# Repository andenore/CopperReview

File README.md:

# CopperReview

[Open CopperReview on GitHub Pages](https://andenore.github.io/CopperReview/).

A review tool for CopperScript designs with two halves that can be open at once:

- **Electrical review** — generated **Schematic** sheets, the **Power** hierarchy and
  **Buses**, from the compiled electrical IR (no layout needed). Double-click or press
  N to note the selection; notes show as numbered markers. See the
  [electrical workflow and contracts](docs/electrical-review.md).
- **Layout review** — the board's placement and routing from a CopperScript board
  export: select components, nets and regions, annotate them, and export a review for
  the next LLM-assisted solver iteration.

**Assembly** (A) uses the same board to track a manual build part by part; see
[Assembly tracking](#assembly-tracking). A CopperScript run's `route-report.json` adds an
**EMI screening** layer to the board: hot loop, switch-node copper and victim pads with the
findings' numbers and conducted spectrum, all screening estimates; see
[EMI screening](#emi-screening). **Simulation** (M) reads a `copper sim` run's
`sim-results.json` on its own, no board needed: benches with their verdicts, failing limits first,
and each bench's plots drawn interactively; see [Simulation results](#simulation-results).

The **Electrical · Layout · Both** switch in the top bar picks what is shown (E, L, B).
**Both** puts the schematic and the board side by side with a draggable divider;
selecting a part or net on either side selects and centres it on the other. Parts
match by CopperScript path (or reference) and nets by name; the top bar counts parts
found on only one side (Both stays off when they share no part), and nothing proves the board was built from that exact source.
Outside **Both**, **Show on board** and **Show in schematic** (S) jump across, and
**Source** opens the declaration in the CopperScript project (found by searching the
compiled sources, since the IR does not record source lines yet), with **Open on
GitHub** at the pinned commit or **Open in VS Code** for a project served locally.

Everything opens from one **Open** menu, or by dropping files on the page:
**File…** (Ctrl+O) recognizes a board export, compiled IR, `.copper` source, saved
scene, layout review, electrical review, CopperScript issue list, run report
(`route-report.json`) or simulation results (`sim-results.json` and its CSVs) by its contents,
and accepts several at once. Opening a board keeps the open schematic, and the other
way round. **Project folder…** compiles a local project (the folder holding
`board.copper` and `copper.mod`) in the browser: sources never leave the computer,
and only dependencies pinned in `copper.lock` are downloaded from GitHub and checked
against the lock; re-pick the folder after editing. **From URL or GitHub…** compiles
GitHub source projects with local imports and pinned dependencies, or opens direct
HTTPS design files; private repositories need a fine-grained token with Contents:
Read-only (⋯ → **Private GitHub access**), kept in the tab and sent only to
`api.github.com`. See [URL loading and provenance](docs/wasm-hosting.md#open-from-url).
**Export** writes the layout review, the electrical review or the board scene; ⋯
holds the compiler check, the review limits and **Dark mode** (the page is light by
default; the choice is remembered in this browser).

This is a **separate Git project**. Its static browser build reuses CopperScript's
Rust compiler, ERC and queries through a bundled WebAssembly worker. No native
CopperScript installation or hosted backend is required by that build. The local
Python 3.11+ server additionally reads raw `.kicad_pcb` files without KiCad.
See [WASM build, static hosting and current boundaries](docs/wasm-hosting.md).
The board is read-only. Feedback never edits the PCB or solver constraints.

## Run

On Ubuntu (or anywhere with `make`, [uv](https://docs.astral.sh/uv/) and Node.js 20+):

```bash
make setup                                   # check tools, install, fetch the browser compiler
make serve PROJECT=../BysseControl-32        # compile a project folder; reload to recompile
make serve PROJECT=../BysseControl-32 HOST=0.0.0.0 OPEN=no   # reachable from other machines
make serve PROJECT=../BysseControl-32 BOARD=../BysseControl-32/build/board.kicad_pcb   # schematic and board, linked
make serve IR=build/electrical.ir.json       # or a compiled IR; BOARD=… alone for a PCB
make serve BOARD=run/board.kicad_pcb REPORT=run/route-report.json   # board with its EMI screening
make serve SIM=build/sim/sim-results.json    # a copper sim run in the Simulation view
make test
```

`PORT` (default 8769), `ENTRY` (board file in a multi-board project) and `STAGE`
(for `BOARD`) are also accepted; `make help` lists the targets. The compiler is
fetched on first use and again whenever `.copperscript-version` changes.

Or run the commands directly. From this repository:

```powershell
python -m copper_review "../CopperAssetTracker/build/placed.kicad_pcb" --stage placed
```

Or use uv to install the local package and run its command:

```powershell
uv run copper-review "../CopperAssetTracker/build/fabrication-review-20261010/finished-routed.kicad_pcb" --stage fully_routed
```

Open the included synthetic example:

```powershell
python -m copper_review examples/demo.kicad_pcb --stage partially_routed
```

Omit the board argument to start with a file picker. `--no-browser` prints the
local URL instead of opening it. `--port 8769` selects a stable port; otherwise
the operating system chooses a free one. Ctrl+C stops the local server.

To attach a source file identity to feedback:

```powershell
python -m copper_review path/to/board.kicad_pcb --source path/to/board.copper --stage partially_routed
```

`--source` records the filename and SHA-256 of that file. It does not compile
the source or establish the identity of transitive dependencies. Existing
CopperScript export commands produce the input; no compiler changes are needed.

To serve a CopperScript project folder and compile it in the browser:

```powershell
npm run fetch:wasm   # once: download the published browser compiler
uv run copper-review --project ../BysseControl-32 --port 8769
```

The server lists and serves only the folder's `.copper` sources,
`copper.mod` / `copper.lock` and `assembly.lock` (skipping `.git`, `.copper-cache`, `node_modules`,
`target` and symlinks), read fresh on every request and only with the session
token. The page compiles them on load, so **reload after editing to recompile**.
Dependencies pinned in `copper.lock` are downloaded from GitHub and checked against
the lock. `--entry boards/main/board.copper` picks the board when the folder has
several; otherwise the page asks.

`--host 0.0.0.0` listens on your network as well and prints a `network:` link per
address. It is plain HTTP: anyone holding the link (with its token) can read the
design and, with `--project`, its sources, so use it only on networks you trust.
The API still requires the token; static files do not. Hashing and note IDs fall
back to built-in implementations because browsers withhold `crypto.subtle` from
non-HTTPS network addresses.

## EMI screening

`copper emi-check` and `copper route-board` store EMI screening in the run's
`route-report.json`, key `emi` (there is no sidecar file). Open the board, then the report
(**Open → File…**, or drop both; also in the static build), or serve both:
`copper-review run/board.kicad_pcb --route-report run/route-report.json`. Try
`python -m copper_review examples/emi-buck.kicad_pcb --route-report examples/emi-buck.route-report.json`
(CopperScript's `examples/emi_buck`, routed; the report trimmed to its `emi` section). `examples/emi-buck.review.json` is a review with a cited finding.

The **EMI** button opens a panel with the converter cells, each finding's key numbers
(hot-loop inductance, worst conducted harmonic with its margin, anti-resonances, switch-node
copper, proximity distances), the assumptions in plain sentences, what is not modelled and the
conducted spectrum with its limit lines. The **EMI screening overlay** layer draws the hot loop
(solid on the component layer, dashed on another, rings at vias), switch-node copper and
the victim pads with their distances; selecting a finding zooms to it, and clicking the overlay
selects the finding. **Cite in layout note** puts a finding in a note and in the exported review.

These are **screening estimates, not a compliance measurement**: they rank likely noise sources and
are never a pass or fail. A report without an `emi` section, or from an older CopperScript, opens
with a note saying what is missing. See [EMI screening review](docs/emi-review.md) and the
[review contract](docs/review-format.md#emi-findings).

## Simulation results

`copper sim BOARD` writes `sim-results.json` (schema `copperscript-sim/v1`) with a page and CSV per
bench. Open the JSON (**Open → File…**, or drop it; also in the static build), serve it with
`copper-review --sim-results build/sim/sim-results.json`, or try **Open → Example simulation**
(CopperScript's `examples/simulation/howland_pump` run, self-written models, bundled as
`copper_review/web/example.sim-results.json`).

The **Simulation** mode lists the benches with pass, fail, error or *no limits* (nothing judged) and
opens on an overview with the failing limits first. A bench shows its plots on a shared axis (Bode
magnitude and phase, noise densities, transient waveforms, stepped families), with a cursor readout,
cursors A and B with their difference, box zoom, pan and log axes where the data is log, steps and
plots toggled from the legend; then spectra (dBc against the fundamental, integration floor shaded),
the measures with value, limit and margin per step, noise contributors, the pole map, Monte Carlo
histograms or worst-case corners, rail currents, component stress and the solver's notes (such as a
steady-state fallback). Light and dark themes and narrow windows are supported.

The JSON already carries every vector the CSVs hold; a CSV is only needed for a file that lacks some,
and the bench then names it. A file of another schema version is refused with a message. Nothing is
re-simulated or checked against an open design. See [Simulation results review](docs/simulation-review.md).

## Review workflow

1. Open an exported board. Choose its review stage explicitly.
2. Pick **Component** to click pads/bodies, or choose a reference in the explorer.
   Pick **Net** to click a pad, track, via, or stored copper fill; the Nets list
   also lets you select a net without visible copper. Shift-click adds/removes
   selections. Component and net selections can be combined.
3. Pick **Region** and drag a rectangle. Shift-drag retains component/net
   selections alongside the region. Coordinates use the native PCB origin,
   millimetres, x right, y down, and a front view for all layers.
4. Write what you observe and the behavior you want improved. Choose category,
   priority, and status; click **Add annotation**. Use **Board-wide observation**
   for a feature request that does not refer to specific geometry.
   To tie a note to a CopperScript run, save the run's issue list with
   `copper issues RUN --json > issues.json` and open it (**Open → File…**). Issue
   windows are drawn on the board and listed in the **Issues** tab; clicking one
   frames it, selects its window as a region and fills **Cites CopperScript
   issues**. The list is rejected when its board hash differs from the open board.
5. Click a saved note to inspect/edit it. Set it to resolved when addressed.
   Add a review summary and **Export → Layout review JSON** or **Copy layout review JSON**.
6. Paste the file contents into an LLM prompt with the relevant CopperScript
   checkout/source available. For example:

   > Use this CopperReview feedback to plan and implement generic placement and
   > routing improvements in CopperScript. Verify the board/source hashes before
   > reproducing the findings. Treat the notes as observations and desired
   > behavior. Build a small reproducer, preserve existing placement/macro intent,
   > and test the algorithm rather than adding a board-specific repair.

Review files are saved as `<board>.review.json`, schema `copper-review/v2`.
See [the output contract](docs/review-format.md), [JSON Schema](docs/review.schema.json),
and [the complete example review](examples/demo.review.json).

Open a saved review (**Open → File…**) to resume notes after opening the exact matching PCB.
Reviews for a different board hash are rejected. **Export → Board scene** writes a
portable `<board>.scene.json`, containing the normalized geometry. Open that
scene on another computer, then load its review. The scene is for the viewer;
the review is the file to paste into a prompt. Native object UUIDs, component
references, CopperScript paths, and net names are retained in both.

## Assembly tracking

**Assembly** (A) tracks a manual build of the open board, part by part. It works
from the board export alone (parts grouped by value and footprint), but is meant
to be used with the project's `assembly.lock`, which adds manufacturer, MPN,
supplier and how each part reaches the board: fitted by hand, by the assembler
(inspect only) or not fitted (confirm the footprint is empty). Values come from
the board.

- With `--project` (or **Open → Project folder…**), the `assembly.lock` beside the
  board source is picked up automatically and read fresh on every reload.
- Otherwise open the board, then `assembly.lock` (**Open → File…**, or drop both).

The lock is read as it is: `copper assembly check` does not run in the browser,
so unreviewed selections are listed but selections out of date with the source
are not detected. For a checked input, CopperScript writes the same content as a
sheet that is only produced when the check passes, and it opens the same way:

```sh
copper assembly bom board.copper --locked --offline --lock assembly.lock -o build/bom.csv \
    --assembly-sheet build/assembly-sheet.json
```

A lock and the sheet written from it name each part the same way, so either can
replace the other without losing progress; a sheet you open is not replaced by the
project's lock. Parts match the board by CopperScript path, then designator; parts
missing from the board and board footprints missing from the lock are listed under
**Assembly details & limits**. Try it with `examples/demo.kicad_pcb` and
`examples/demo.assembly.lock` (or `examples/demo.assembly-sheet.json`).

The plan lists one line per identical part on one side, in passes: SMD on the
side with fewer hand-placed parts first, then the other side, then through-hole,
then assembler-fitted and not-fitted parts. Within a pass, small bodies come
first. Only the side being assembled is drawn (the current line's side; through-hole
parts go in from their own side), with through-hole pads and drills still shown.
The current line's parts are outlined with pin 1 (the pad numbered 1 or A1) ringed.

The **Realistic** look (V, on by default here) draws that side as the board
looks: solder mask over raised copper, exposed pads, white silkscreen and grey
paste on every stencil aperture. Fitted parts get solder on their pads and a body
with a shadow (the fabrication outline, else the span of the pads). It is a
picture, not a check: mask expansion, paste reduction and body heights are not
modelled. Switch it off for the plain view, where placed parts turn green and
copper is dimmed. The board turns over with the work: a back-side line is seen
from the back, mirrored as it is on the bench, and a front-side line from the
front. **Flip** (T) turns it over by hand.
Each part of the current line carries a badge with its reference and value; the
selected part's is filled, and a part out of view keeps its badge at the edge of
the view with an arrow towards it. When zoomed in, a **minimap** in the corner
(sized to the view) shows the whole side, the current
line's parts and where the view is; click or drag in it to move the view.

- **Space** marks the line placed and moves to the next open line, **I** marks it
  inspected, **J/K** or **↓/↑** step, **Z** zooms to its parts, **F** fits the board.
  Changing line selects its first part still to place and zooms to it; when every
  part of the line is done, the view frames them all instead.
- **→** / **←** (or **N** / **Shift+N**) step through the parts of the current line, panning to each,
  since identical parts can be spread over the board. **X** marks the selected part
  and moves to the next open one.
- Click a part on the board or in the list to set its own status, flag it
  **Needs rework** (P) and add a note; **Add as layout note** carries the note
  into the layout review. Double-click toggles a single part.
- Progress saves in this browser per board file. **Export → Assembly progress**
  writes `<board>.assembly.json` (`copper-review-assembly/v1`) with the sheet,
  to continue on another device; it only opens with the same board file. A part's
  progress is kept only while its sheet selection digest, MPN and footprint are
  unchanged, so a changed selection starts again and is listed.

Ticks record what was done at the bench. They do not verify placement,
orientation or solder joints, and nothing proves the board was built from the
sheet's source.

## Mechanical review and constraint feedback

Inspect the exported board outline, cutouts, footprint geometry, drills and
keepouts alongside placed components and copper. Use a **Mechanical** annotation
to record connector placement, mounting clearance or other visible fit concerns;
select the affected component or region so the feedback keeps its exact board
identity and geometry.

Geometry and constraint authoring belong in CopperScript's
[mechanical/floorplan editor](https://github.com/andenore/CopperScript/blob/main/docs/mechanical-editor.md).
There you can preview placement and review source changes for board geometry,
poses and supported constraints. CopperReview supplies observations for that next
iteration; it does not edit `.copper` intent, enforce solver constraints or verify
3D enclosure clearance. Features absent from the PCB export cannot be recovered
from the drawing alone.

## 3D view

The **3D** button draws a body for every component (drag orbits, shift or
right-drag pans, wheel zooms). Views snap with numpad-style keys, as in common CAD
tools (digit or numpad keys):

| Key | View |
| --- | --- |
| **7** / **Shift+7** | top / bottom |
| **1** / **Shift+1** | front (from the board's bottom edge) / back |
| **3** / **Shift+3** | right / left |
| **Home** | reset to the top view |
| **5** or **O** | orthographic or perspective (also the **Ortho** button; remembered) |

An indicator in the corner shows the board's axes as the camera sees them (X right,
Y towards the board's top edge, Z out of the top side), the named view or "Free",
and the projection; click an axis end to look from it. **Flip** turns the board
over and stays in step with the 2D flip.

Where each body comes from, in order:

1. `copper-review BOARD.kicad_pcb` serves the `*.3dshapes/*.wrl` files beside the
   board. A CopperScript export writes one per footprint into
   `CopperScript.3dshapes/`, the same files KiCad shows.
2. Otherwise the viewer asks CopperScript's WASM build (`generate_body`) to
   generate the body from the footprint geometry the scene carries
   (`body_input`: pads, fabrication and courtyard outline, height). This works
   in the hosted viewer and for boards opened from a file or exported scene.

Bodies from step 2 are approximate and counted as such in the status line. The
viewer never rebuilds bodies itself; the compiler's generator is the only one.

KiCad's own models (a CopperScript export copies them into `CopperScript.3dshapes/`
as STEP) are drawn with [occt-import-js](https://github.com/kovacsv/occt-import-js),
OpenCascade compiled to WASM. It is licensed LGPL-2.1, is about 8 MB, and is
fetched at build time with `npm run build:occt` (pinned by npm's integrity hash,
never committed, loaded only when a STEP model is shown; the licence files are
kept beside it in `copper_review/web/occt/`). Without it the generated body
stands in and the status line says why.

Limits: only VRML and STEP files from `.3dshapes` folders next to the board are
read, so STEP models need `copper-review BOARD.kicad_pcb` (the hosted viewer has no
board folder and shows the generated body); the board is its
bounding rectangle at an assumed 1.6 mm; back-side parts and non-zero model
rotation or offset are placed best-effort and have not been compared with KiCad.
Scenes exported before `body_input` existed, and boards compiled from `.copper`
source in the browser, carry no footprint geometry and show no 3D bodies. The
pinned WASM build must include `generate_body`; an older one reports that it
cannot generate bodies.

## Viewing and storage

- Wheel: zoom under the pointer. Right/middle-drag: pan. **Fit board**: overview.
- Keyboard: C component, N net, R region, F fit, V realistic look, T flip, Escape clear (outside form fields).
- **Flip** (T) turns the board over: it is seen from the back, mirrored left to right about
  its centre line, with labels kept readable; the realistic look then shows the back side.
  Coordinates, notes and exports stay in the native front-view frame; the status bar says
  "from back (mirrored)" while it is on.
- **Realistic** draws the visible side as the board looks (mask, silkscreen, metal pads and
  fitted bodies); the choice is remembered per mode. The minimap appears when zoomed in.
- Pads keep their paste and mask layers (`paste_layers`, `mask_layers`, per side). Scenes
  exported before these fields existed assume paste on every outer SMD pad.
- Reference labels never overlap: selected parts and larger bodies win, and the
  status bar counts labels waiting for more zoom.
- Toggle copper layers, reference labels, logical net guides, fills/zone intent,
  or isolate selected nets. Hidden layers remain in explicitly selected net
  snapshots; region queries use the visible layers recorded with the note.
- Pad labels show the number and native pin name, falling back to the net name
  when the PCB has no `pinfunction` field. Labels appear as you zoom in or focus
  a component/net; pad hover always shows the full identity. Toggle them with
  **Pad numbers / names**. Label text stays upright even on rotated pads.
- Hover a pad, track, via, copper fill, or net in the explorer to highlight that
  net's visible pads, tracks, vias, and fills without changing your selection.
- Notes auto-save in browser local storage under the exact board hash. The same
  local port/browser profile is needed to reuse that storage. Export JSON for
  durable storage and sharing; local storage may be unavailable or reach quota.
- All parsing and rendering happens locally. The server binds only to
  `127.0.0.1`, requires a session token for API calls, rejects cross-origin
  requests, and exposes only its own web assets. Files are never uploaded to an
  external service. The UI importer has a 49 MiB input limit; CLI limit is 50 MiB.

## Geometry and limits

Supported: front/back footprints and their local graphics; circular, oval,
rectangular and rounded pads; through/NPTH drills; straight and modern arc
tracks; through/blind/buried via layer spans; polygon/line/arc/circle outlines and
cutouts; board and footprint zones (stored in board coordinates) as intent,
keepouts and stored filled polygons; footprints with blank or repeated references
(named `<reference or footprint>#n`, original kept as `native_reference`);
and filled netted graphic copper exported by CopperScript. Curves are sampled
with at most 0.01 mm chord error. Stored polygons are rendered as stored, including
linked hole contours. Region intersections conservatively use pad bounding
polygons and stroke-expanded boxes, so boundary hits can include nearby objects.
Filled areas use even/odd hole rendering and are not outlined: the retraced
connectors used to store hole contours are not physical edges or tracks.

There is no DRC or connectivity solver. Logical net guides display membership,
including already connected pads; they are not a verified ratsnest or open-net
count. Fully routed is a reviewer declaration. Copper fills are not recomputed.
Non-copper text labels/dimensions are omitted, and 3D models are only drawn in the 3D view (see
[3D view](#3d-view)); custom/trapezoidal
pads use bounding rectangles with visible import warnings. Legacy arc syntax
is rejected; Bezier graphics are reported as unsupported. The importer targets
modern CopperScript exports, not every possible KiCad construct. Electrical-only
`board.json` opens in electrical review when it is a compiled CopperScript board
IR; it supplies no PCB geometry. `.copper` source files must be compiled externally.

## Development

```powershell
python -m unittest discover -s tests -v
node --test tests/core.test.js tests/emi.test.js tests/sim.test.js tests/electrical.test.js tests/topology.test.js tests/compiler.test.js
```

Browser integration test (optional Playwright installation, not a runtime
dependency): start the demo server, then:

```powershell
node tests/browser.mjs "http://127.0.0.1:PORT/#token=TOKEN"
```

`COPPER_PLAYWRIGHT_MODULE` can point to an existing Playwright package;
`COPPER_BROWSER_EXECUTABLE` can point to an installed Chrome/Chromium executable.
The test verifies component/net/region annotations, geometry exports, edit/delete,
review import, persistence, layer controls, and search. Artifacts go to ignored
`test-results/`.
`node tests/flip-browser.mjs URL` checks picking and side-following on a flipped board.
`node tests/views3d-browser.mjs URL` checks the 3D view keys, projection and indicator
(it needs the browser compiler, like the 3D view).
`node tests/assembly-browser.mjs URL` checks assembly mode: planning with and without
the demo sheet, marking, rework notes, persistence, progress export and import.
`node tests/viewer-regressions.mjs "http://127.0.0.1:PORT/#token=TOKEN"` additionally
checks linked-fill holes/connector pixels, pad labels, and transient whole-net hover;
`node tests/issues-labels.mjs URL` checks issue loading/citation and label thinning.
`node tests/emi-browser.mjs "http://127.0.0.1:PORT/#token=TOKEN"` checks the EMI layer, panel, citing and export on a
server started on `examples/emi-buck.kicad_pcb` with `--route-report examples/emi-buck.route-report.json` (see the script's header).
`tests/fixtures/kicad-conformance` is a KiCad 9 board with hand-derived expectations
shared with CopperScript's KiCad reader (keep both copies identical).

The project uses Python's standard library, buildless ES modules, and Canvas 2D.
`copper_review/importer.py` is the file-to-scene adapter; `web/core.js` owns the
geometry query and review contract; `web/app.js` owns interactions and rendering.

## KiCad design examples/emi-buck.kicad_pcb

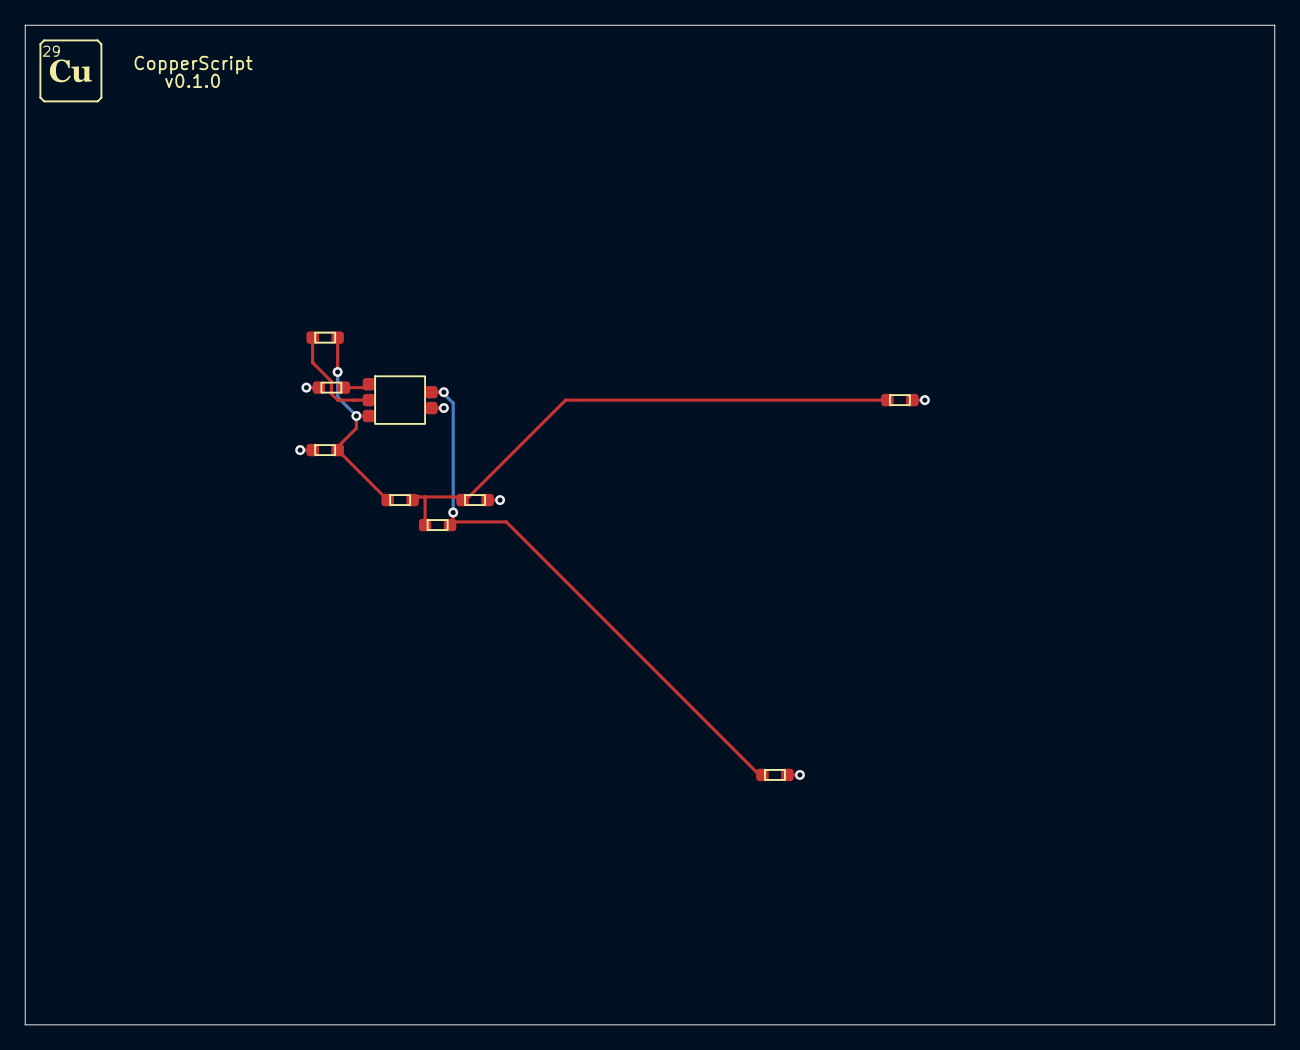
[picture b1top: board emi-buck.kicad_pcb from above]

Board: 4 copper layers, 100.0 x 80.0 mm, 9 parts (0 on the bottom side), 6 nets.

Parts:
CBOOT: 100 nF; C_0402_319a789b69__58f2677de6bb3c9b0893
CIN: 10 uF; C_0805_c031770aba__1ec4d6ade0683a1ceece
COUT: 22 uF; C_0805_c031770aba__1ec4d6ade0683a1ceece
D1: Diode; SOD_123_463054056f__f90e3be13c9360126425
J1: Conn; PinHeader_1x02_2a7c6393d3__3d_ae730b169e22__7bf14a1eef909aa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
L1: 4.7 uH; L_1210_ae6afbd5a7__c462db8df63e6d82ad8f
R1: 100 kohm; R_0402_45521d2bcd__488496eda3cd49d8c580
R2: 33 kohm; R_0402_45521d2bcd__488496eda3cd49d8c580
U1: Buck; QFN_5_bccb3b6db4__a0be85da01b5000b1b32

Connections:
BOOT: CBOOT.1, U1.2
FB: R1.2, R2.1, U1.4
GND: CIN.2, COUT.2, D1.1, J1.2, R2.2, U1.5
SW: CBOOT.2, D1.2, L1.1, U1.3
VIN: CIN.1, U1.1
VOUT: COUT.1, J1.1, L1.2, R1.1

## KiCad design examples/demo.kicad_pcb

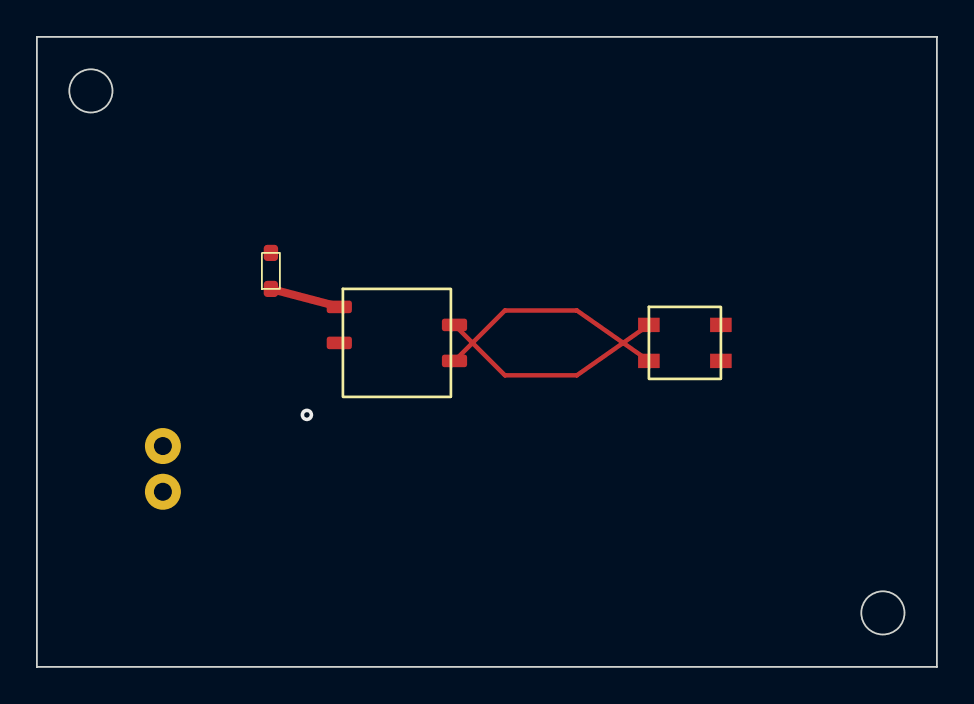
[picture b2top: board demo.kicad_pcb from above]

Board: 2 copper layers, 50.0 x 35.0 mm, 4 parts (1 on the bottom side), 4 nets.

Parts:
C1: 100 nF; Capacitor
J1: Power in; Connector
U1: Controller
U2: Sensor

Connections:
+3V3: C1.1, J1.1, U1.1, U2.3
GND: C1.2, J1.2, U1.2, U2.4
SENSOR_SCL: U1.3, U2.1
SENSOR_SDA: U1.4, U2.2
